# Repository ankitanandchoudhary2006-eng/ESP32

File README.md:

# ESP32

So I made a custom devboard based on ESp-Wroom-32 . It has a USB-C for power and signal and has interval voltage regulator to regulate the voltage down to 3.3V prior to that we have onboard LEDs and  USB to UART circuit and it has 2 sets of 15 connectors that connectes to power , gnd and multiple pins on the ESP32.

## features 
- Based onc interface
-   ESP - WROOM -32
- Has USB-C interface
- Has 3.3V voltage regulator
- Has USB to UART  circuit

# Schamtics 

# PCB

# CAD

# BOM

| Category | Component / Charge | Designator | Quantity | Total Price (USD) | Link | Note |
|---|---|---|---:|---:|---|---|
| Component | 100nF ceramic capacitor | C1,C3,C4,C5,C6 | 25 | 0.1375 | https://jlcpcb.com/partdetail/YAGEO-CC0603KRX7R9BB104/C14663 | YAGEO CC0603KRX7R9BB104 |
| Component | 10uF/16V aluminum electrolytic capacitor | C2 | 5 | 0.892 | https://jlcpcb.com/partdetail/HonorElec-UD2E100M1010/C88697 | Honor Elec UD2E100M1010 |
| Component | B5819W Schottky diode | D1 | 20 | 0.344 | https://jlcpcb.com/partdetail/hongjiacheng-B5819W/C7420330 | hongjiacheng B5819W |
| Component | Red 0603 LED | D2 | 20 | 0.074 | https://jlcpcb.com/partdetail/XINGLIGHT-XL_1608SURC06/C965799 | XINGLIGHT XL-1608SURC-06 |
| Component | Blue 0603 LED | D3 | 20 | 0.082 | https://jlcpcb.com/partdetail/XINGLIGHT-XL_1608UBC04/C965807 | XINGLIGHT XL-1608UBC-04 |
| Component | USB-C receptacle, USB 2.0, 16-pin | J1 | 2 | 4.1262 | https://jlcpcb.com/partdetail/XKBConnection-USB31_TYPE_CFSABC/C2880583 | XKB Connection USB31-TYPE-C-FSABC |
| Component | SS8050 NPN transistor | Q1,Q2 | 12 | 0.1392 | https://jlcpcb.com/partdetail/hongjiacheng-SS8050/C7420370 | hongjiacheng SS8050 |
| Component | 5.1kΩ resistor, 0603 | R1,R2 | 20 | 0.03 | https://jlcpcb.com/partdetail/23913-0603WAF5101T5E/C23186 | UNI-ROYAL 0603WAF5101T5E |
| Component | 1kΩ resistor, 0603 | R3 | 20 | 0.032 | https://jlcpcb.com/partdetail/21904-0603WAF1001T5E/C21190 | UNI-ROYAL 0603WAF1001T5E |
| Component | 10kΩ resistor, 0603 | R4,R5,R6 | 20 | 0.034 | https://jlcpcb.com/partdetail/26547-0603WAF1002T5E/C25804 | UNI-ROYAL 0603WAF1002T5E |
| Component | 220Ω resistor, 0603 | R7 | 20 | 0.034 | https://jlcpcb.com/partdetail/23689-0603WAF2200T5E/C22962 | UNI-ROYAL 0603WAF2200T5E |
| Component | Push-button switch | SW1,SW2 | 4 | 2.0892 | https://jlcpcb.com/partdetail/55982-DSIC01LHGET/C54957 | DongGuan KINGTEK DSIC01LHGE |
| Component | ESP32-WROOM-32 module | U1 | 2 | 8.892 | https://jlcpcb.com/partdetail/EspressifSystems-ESP32_WROOM_32N4/C82899 | Espressif ESP32-WROOM-32-N4 |
| Component | CH340C USB-to-serial converter | U2 | 2 | 1.1916 | https://jlcpcb.com/partdetail/WCH_Jiangsu_Qin_Heng-CH340C/C7464026 | WCH CH340C |
| Component | AMS1117-3.3 voltage regulator | U3 | 2 | 0.4016 | https://jlcpcb.com/partdetail/Advanced_MonolithicSystems-AMS1117_33/C6186 | Advanced Monolithic Systems AMS1117-3.3 |

## Order Cost

| Category | Component / Charge | Total Price (USD) |
|---|---|---:|
| Order cost | PCB fabrication | 4.00 |
| Order cost | PCBA setup fee | 25.75 |
| Order cost | Stencil | 8.27 |
| Order cost | Panel | 0.00 |
| Order cost | Large size | 0.00 |
| Subtotal (informational) | Components subtotal (15 items) | 18.50 |
| Order cost | Feeders loading fee | 21.70 |
| Order cost | SMT assembly | 0.94 |
| Order cost | Hand-soldering labor fee | 3.61 |
| Order cost | Manual assembly | 0.40 |
| Order cost | Packaging fee | 0.50 |
| Order cost | Special components fee | 0.06 |
| Shipping | Shipping | 9.27 |
| Discount | Discount | -10.00 |
| **Total** | **Grand Total** | **83.00** |

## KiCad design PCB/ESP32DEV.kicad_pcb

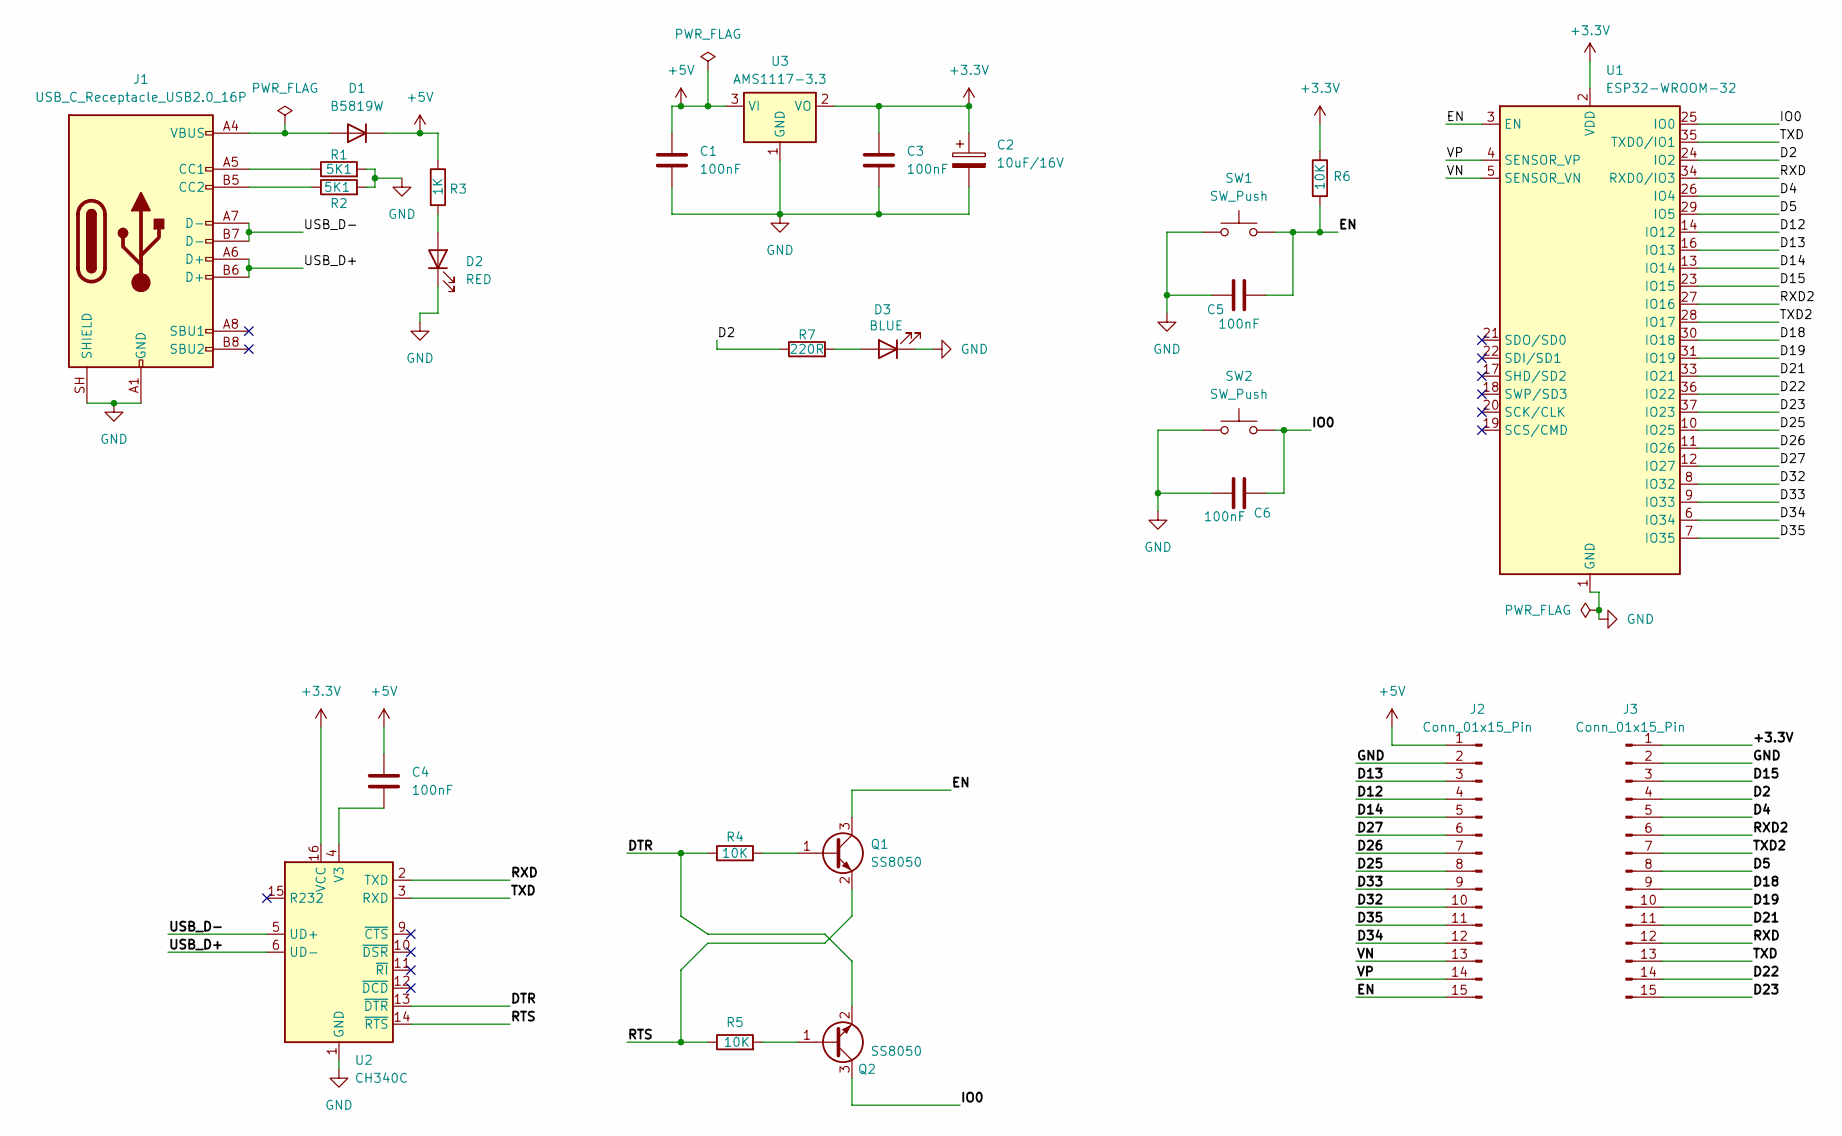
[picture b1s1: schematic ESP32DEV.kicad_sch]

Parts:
C1, C3, C4, C5, C6: 100nF; C_0603_1608Metric
C2: 10uF/16V; CP_EIA-3216-10_Kemet-I
D1: B5819W; D_SOD-123
D2: RED; LED_0603_1608Metric
D3: BLUE; LED_0603_1608Metric
J1: USB_C_Receptacle_USB2.0_16P; USB_C_Receptacle_HRO_TYPE-C-31-M-12
J2, J3: Conn_01x15_Pin; PinHeader_1x15_P2.54mm_Vertical
Q1, Q2: SS8050; SOT-23
R1, R2: 5K1; R_0603_1608Metric
R3: 1K; R_0603_1608Metric
R4, R5, R6: 10K; R_0603_1608Metric
R7: 220R; R_0603_1608Metric
SW1, SW2: SW_Push; SW_Push_SPST_NO_Alps_SKRK
U1: ESP32-WROOM-32
U2: CH340C; SOIC-16_3.9x9.9mm_P1.27mm
U3: AMS1117-3.3; SOT-223-3_TabPin2

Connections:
+3.3V: C2.1, C3.1, J3.1, R6.1, U1.2 (VDD_2), U2.16 (VCC), U3.2 (VO)
+5V: C1.1, C4.1, D1.1 (K), J2.1, R3.1, U3.3 (VI)
/D2: J3.4, R7.1, U1.24 (IO2_24)
/D4: J3.5, U1.26 (IO4_26)
/D5: J3.8, U1.29 (IO5_29)
/D12: J2.4, U1.14 (IO12_14)
/D13: J2.3, U1.16 (IO13_16)
/D14: J2.5, U1.13 (IO14_13)
/D15: J3.3, U1.23 (IO15_23)
/D18: J3.9, U1.30 (IO18_30)
/D19: J3.10, U1.31 (IO19_31)
/D21: J3.11, U1.33 (IO21_33)
/D22: J3.14, U1.36 (IO22_36)
/D23: J3.15, U1.37 (IO23_37)
/D25: J2.8, U1.10 (IO25_10)
/D26: J2.7, U1.11 (IO26_11)
/D27: J2.6, U1.12 (IO27_12)
/D32: J2.10, U1.8 (IO32_8)
/D33: J2.9, U1.9 (IO33_9)
/D34: J2.12, U1.6 (IO34_6)
/D35: J2.11, U1.7 (IO35_7)
/DTR: Q2.2 (E), R4.1, U2.13 (~DTR)
/EN: C5.1, J2.15, Q1.3 (C), R6.2, SW1.2, U1.3 (EN_3)
/IO0: C6.1, Q2.3 (C), SW2.2, U1.25 (IO0_25)
/RTS: Q1.2 (E), R5.1, U2.14 (~RTS)
/RXD: J3.12, U1.34 (RXD0/IO3_34), U2.2 (TXD)
/RXD2: J3.6, U1.27 (IO16_27)
/TXD: J3.13, U1.35 (TXD0/IO1_35), U2.3 (RXD)
/TXD2: J3.7, U1.28 (IO17_28)
/USB_D+: J1.A6 (D+), J1.B6 (D+), U2.6 (UD-)
/USB_D-: J1.A7 (D-), J1.B7 (D-), U2.5 (UD+)
/VN: J2.13, U1.5 (SENSOR_VN_5)
/VP: J2.14, U1.4 (SENSOR_VP_4)
GND: C1.2, C2.2, C3.2, C5.2, C6.2, D2.1 (K), D3.1 (K), J1.A1 (GND), J1.A12 (GND), J1.B1 (GND), J1.B12 (GND), J1.SH (SHIELD), J2.2, J3.2, R1.2, R2.2, SW1.1, SW2.1, U1.0.35 (GND_39), U1.1 (GND_1), U1.15 (GND_15), U1.38 (GND_38), U1.39 (GND_39), U2.1 (GND), U3.1 (GND)
unnamed: D2.2 (A), R3.2
unnamed: D3.2 (A), R7.2
unnamed: J1.A5 (CC1), R1.1
unnamed: J1.B5 (CC2), R2.1
unnamed: Q1.1 (B), R4.2
unnamed: Q2.1 (B), R5.2
unnamed: C4.2, U2.4 (V3)
VBUS: D1.2 (A), J1.A4 (VBUS), J1.A9 (VBUS), J1.B4 (VBUS), J1.B9 (VBUS)

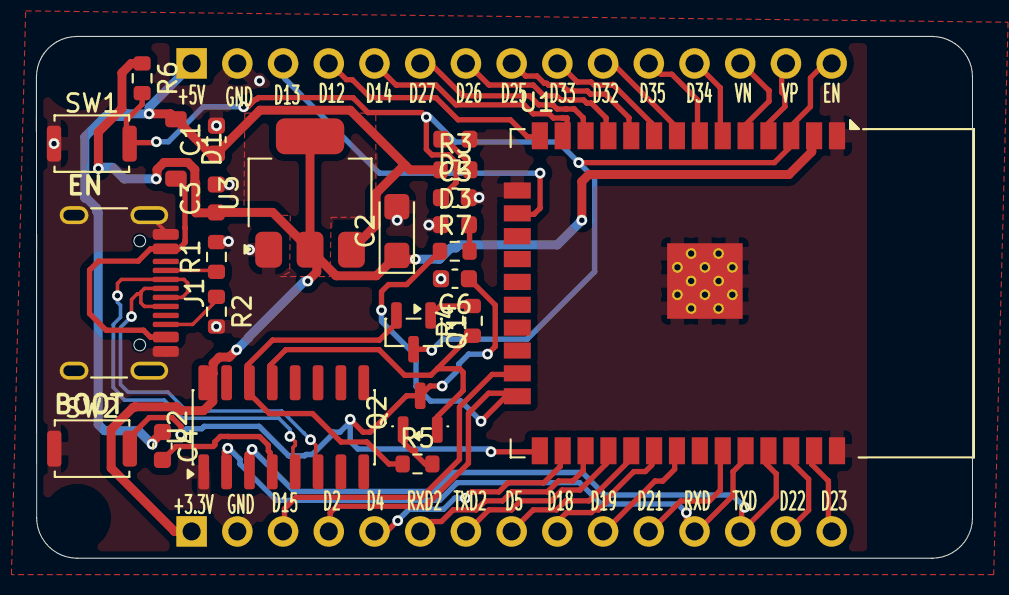
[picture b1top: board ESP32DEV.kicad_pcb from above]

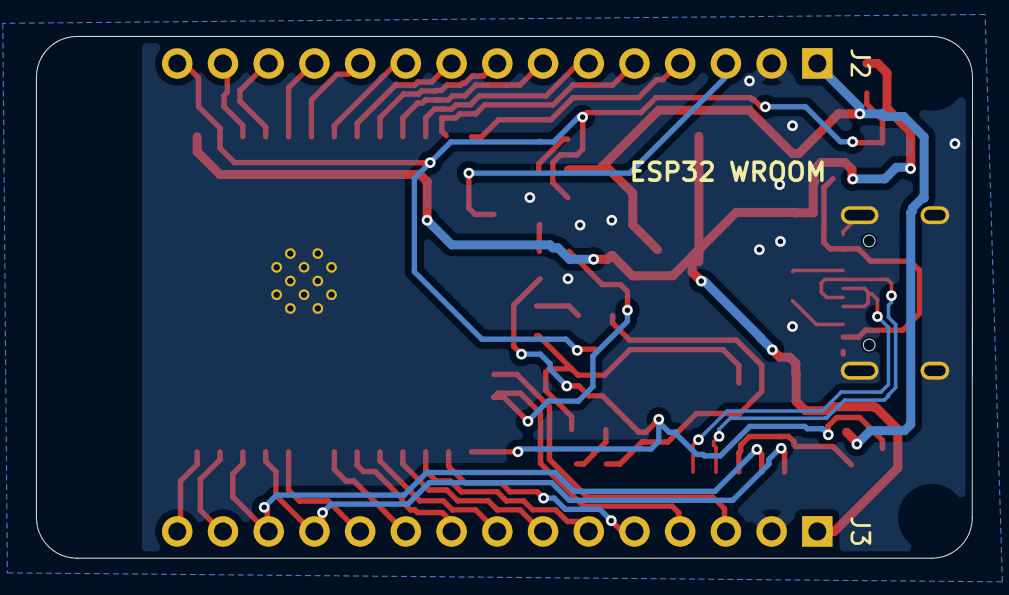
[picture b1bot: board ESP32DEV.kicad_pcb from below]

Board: 2 copper layers, 52.0 x 29.0 mm, 26 parts (2 on the bottom side), 42 nets.

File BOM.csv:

Category,Component / Charge,Designator,Quantity,Total Price (USD),Link,Notes
Component,100nF ceramic capacitor,"C1,C3,C4,C5,C6",25,0.1375,https://jlcpcb.com/partdetail/YAGEO-CC0603KRX7R9BB104/C14663,YAGEO CC0603KRX7R9BB104; JLCPCB C14663
Component,10uF/16V aluminum electrolytic capacitor,C2,5,0.892,https://jlcpcb.com/partdetail/HonorElec-UD2E100M1010/C88697,Honor Elec UD2E100M1010; JLCPCB C88697
Component,B5819W Schottky diode,D1,20,0.344,https://jlcpcb.com/partdetail/hongjiacheng-B5819W/C7420330,hongjiacheng B5819W; JLCPCB C7420330
Component,Red 0603 LED,D2,20,0.074,https://jlcpcb.com/partdetail/XINGLIGHT-XL_1608SURC06/C965799,XINGLIGHT XL-1608SURC-06; JLCPCB C965799
Component,Blue 0603 LED,D3,20,0.082,https://jlcpcb.com/partdetail/XINGLIGHT-XL_1608UBC04/C965807,XINGLIGHT XL-1608UBC-04; JLCPCB C965807
Component,"USB-C receptacle, USB 2.0, 16-pin",J1,2,4.1262,https://jlcpcb.com/partdetail/XKBConnection-USB31_TYPE_CFSAB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,XKB Connection USB31-TYPE-C-FSABC; JLCPCB C2880583
Component,SS8050 NPN transistor,"Q1,Q2",12,0.1392,https://jlcpcb.com/partdetail/hongjiacheng-SS8050/C7420370,hongjiacheng SS8050; JLCPCB C7420370
Component,"5.1kΩ resistor, 0603","R1,R2",20,0.03,https://jlcpcb.com/partdetail/23913-0603WAF5101T5E/C23186,UNI-ROYAL 0603WAF5101T5E; JLCPCB C23186; match unconfirmed—comment mismatch warning
Component,"1kΩ resistor, 0603",R3,20,0.032,https://jlcpcb.com/partdetail/21904-0603WAF1001T5E/C21190,UNI-ROYAL 0603WAF1001T5E; JLCPCB C21190; match unconfirmed—comment mismatch warning
Component,"10kΩ resistor, 0603","R4,R5,R6",20,0.034,https://jlcpcb.com/partdetail/26547-0603WAF1002T5E/C25804,UNI-ROYAL 0603WAF1002T5E; JLCPCB C25804; match unconfirmed—comment mismatch warning
Component,"220Ω resistor, 0603",R7,20,0.034,https://jlcpcb.com/partdetail/23689-0603WAF2200T5E/C22962,UNI-ROYAL 0603WAF2200T5E; JLCPCB C22962; match unconfirmed—comment mismatch warning
Component,Push-button switch,"SW1,SW2",4,2.0892,https://jlcpcb.com/partdetail/55982-DSIC01LHGET/C54957,DongGuan KINGTEK DSIC01LHGET; JLCPCB C54957
Component,ESP32-WROOM-32 module,U1,2,8.892,https://jlcpcb.com/partdetail/EspressifSystems-ESP32_WROOM_3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,Espressif ESP32-WROOM-32-N4; JLCPCB C82899; match warning: comment differs from matched part number
Component,CH340C USB-to-serial converter,U2,2,1.1916,https://jlcpcb.com/partdetail/WCH_Jiangsu_Qin_Heng-CH340C/C7464026,WCH CH340C; JLCPCB C7464026
Component,AMS1117-3.3 voltage regulator,U3,2,0.4016,https://jlcpcb.com/partdetail/Advanced_MonolithicSystems-AMS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,Advanced Monolithic Systems AMS1117-3.3; JLCPCB C6186
Order cost,PCB fabrication,,,4.0,,From supplied JLCPCB price screenshot
Order cost,PCBA setup fee,,,25.75,,
Order cost,Stencil,,,8.27,,
Order cost,Panel,,,0.0,,
Order cost,Large size,,,0.0,,
Subtotal (informational),Components subtotal (15 items),,,18.5,,Already itemized in the component rows; do not add twice
Order cost,Feeders loading fee,,,21.7,,
Order cost,SMT assembly,,,0.94,,
Order cost,Hand-soldering labor fee,,,3.61,,
Order cost,Manual assembly,,,0.4,,
Order cost,Packaging fee,,,0.5,,
Order cost,Special components fee,,,0.06,,
Shipping,Shipping,,,9.27,,
Discount,Discount,,,-10.0,,USD 10 discount applied
Total,Grand total,,,83.0,,PCB + PCBA charges (including components once) + shipping - discount
